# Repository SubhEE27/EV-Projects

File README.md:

# ⚡ Electric Vehicle Projects 🚗

This repository showcases my work in **Electric Vehicle (EV) system design**, focusing on **MATLAB/Simulink simulations**, **custom PCB development**, and a **3D CAD model** of an e-rickshaw. These projects combine theoretical modeling with hands-on engineering to develop subsystems of electric mobility solutions.

---

## 🛠️ Technologies & Tools Used

- **Simulation:** MATLAB/Simulink
- **PCB Design:** Autodesk Eagle, Fusion 360 Electronics
- **3D CAD Modeling:** Autodesk Fusion 360
- **Microcontroller Integration:** Arduino, ESP32

---

## 📁 Repository Structure

/MATLAB_Simulations/
├── BLDC_Motor_Control/
├── Power_Management_System/
└── Regenerative_Braking_Model/

/PCB_Designs/
├── Motor_Controller_PCB/
└── Battery_Management_PCB/

/3D_CAD_Model/
└── E_Rickshaw_Model.f3d

---

## ⚙️ Project Highlights

### 🔷 MATLAB/Simulink Simulations

1. **BLDC Motor Control**
   - Implemented 6-step commutation with inverter, PI control loop, and DC-link filtering
   - Simulated torque and speed control for efficient motor drive

---

### 🟢 PCB Development

1. **Motor Controller PCB**
   - Designed multi-layer PCB with gate drivers, MOSFETs, and microcontroller interface
   - Integrated feedback sensors and protection circuitry
     
---

### 🟠 3D CAD: E-Rickshaw Model

- Created a **full 3D assembly model** of an e-rickshaw using **Fusion 360**
- Includes chassis, battery housing, motor mount, and cabin
- Useful for mechanical layout planning and integration with electronics

---

## 🚀 Getting Started

### Requirements
- MATLAB R2021b or later with Simscape and Simulink
- Autodesk Eagle or Fusion 360 for PCB and CAD files
- LTspice (optional for analog circuit validation)

### How to Use
- Open `.slx` files in MATLAB/Simulink to simulate system behavior
- Open `.brd` or `.f3d` files in Eagle or Fusion 360 for design viewing or editing
- Each folder contains documentation, schematics, and simulation data

---

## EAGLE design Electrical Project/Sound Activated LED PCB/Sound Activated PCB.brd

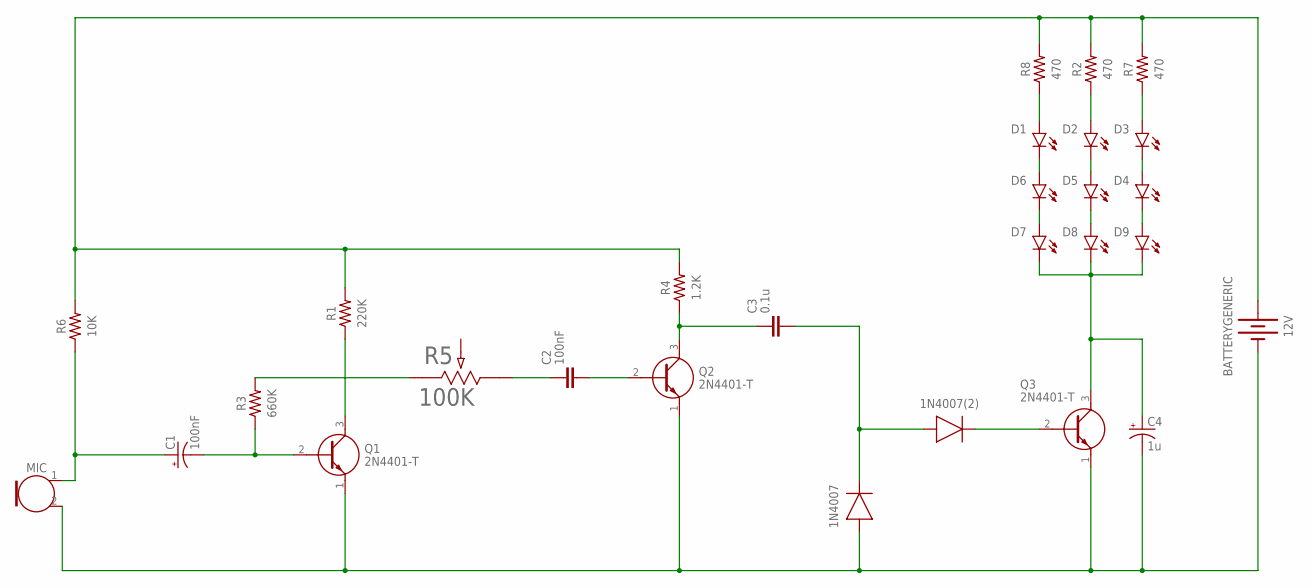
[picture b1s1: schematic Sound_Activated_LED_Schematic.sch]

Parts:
1N4007, 1N4007(2): DIODE_1N4148W-7-F_SOD123G; SOD3715X135
12V: BATTERYGENERIC; BATTERY-GENERIC
C1: 100nF; CAPMP3216X180N
C2: 100nF; CAPC1005X60
C3: 0.1u; CAPC1005X60
C4: 1u; CAPMP3216X180N
D1, D2, D3, D4, D5, D6, D7, D8, D9: CHIP-ROUND-R_0603; LEDC1608X65N_RND-R
MIC: CMA-4544PF-W
Q1, Q2, Q3: 2N4401-T; 2N4401T
R1: 220K; RESC1005X40
R2, R7, R8: 470; RESC1005X40
R3: 660K; RESC1005X40
R4: 1.2K; RESC1005X40
R5: 100K; POT_1623757-2
R6: 10K; RESC1005X40

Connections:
unnamed: C1.1 (+), MIC.1 (OUT), R6.1
unnamed: D1.A, R8.1
unnamed: Q1.3 (C), R1.1
unnamed: 1N4007.2 (A), 12V.-, C4.2 (-), MIC.2 (GND), Q1.1 (E), Q2.1 (E), Q3.1 (E)
unnamed: C1.2 (-), Q1.2 (B), R3.1
unnamed: R3.2, R5.1
unnamed: C2.1, R5.3
unnamed: C2.2, Q2.2 (B)
unnamed: C3.1, Q2.3 (C), R4.1
unnamed: 12V.+, R1.2, R2.2, R4.2, R6.2, R7.2, R8.2
unnamed: D2.A, R2.1
unnamed: D3.A, R7.1
unnamed: D1.C, D6.A
unnamed: D2.C, D5.A
unnamed: D3.C, D4.A
unnamed: D6.C, D7.A
unnamed: D5.C, D8.A
unnamed: D4.C, D9.A
unnamed: C4.1 (+), D7.C, D8.C, D9.C, Q3.3 (C)
unnamed: 1N4007.1 (C), 1N4007(2).2 (A), C3.2
unnamed: 1N4007(2).1 (C), Q3.2 (B)

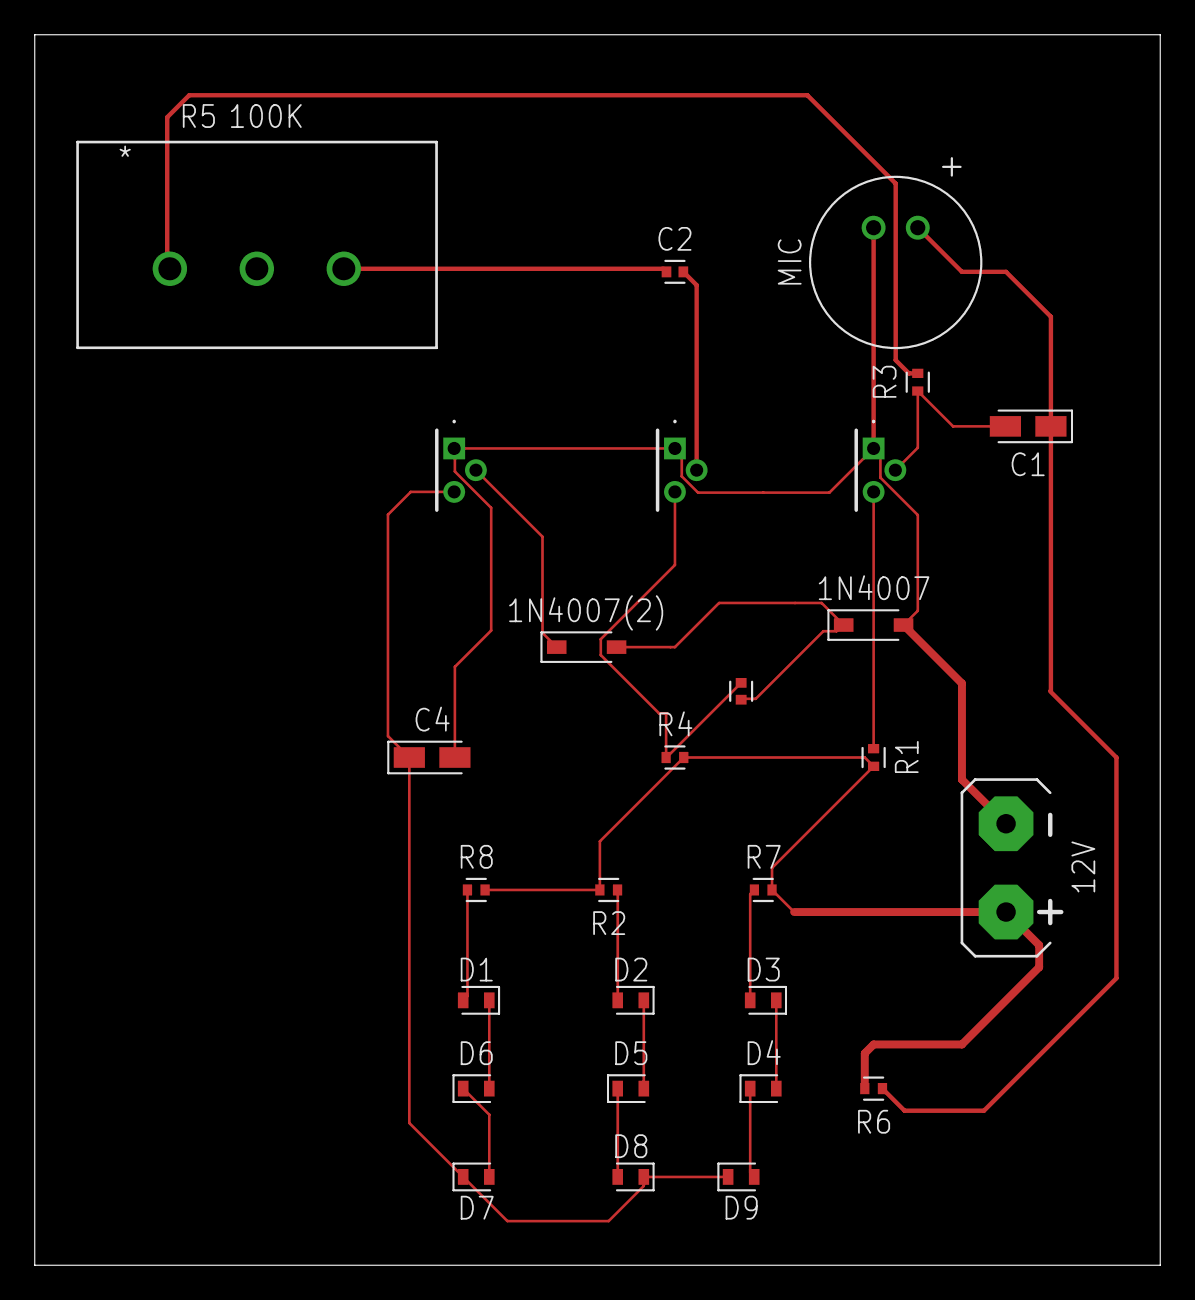
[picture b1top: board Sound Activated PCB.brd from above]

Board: 2 copper layers, 64.8 x 70.8 mm, 28 parts (0 on the bottom side), 21 nets.

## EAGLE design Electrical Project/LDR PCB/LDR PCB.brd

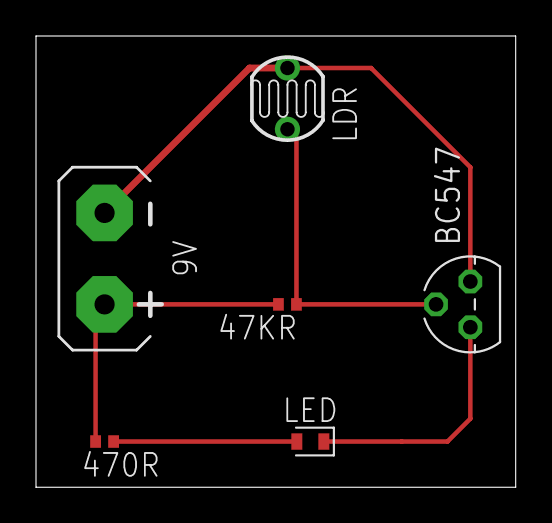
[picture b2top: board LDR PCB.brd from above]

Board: 2 copper layers, 26.6 x 25.1 mm, 6 parts (0 on the bottom side), 5 nets.

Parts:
9V: BATTERY-9VGENERIC; BATTERY-GENERIC
47KR: 47K; R0402
470R: 470; R0402
BC547: BC547; TO92
LDR: PHOTOCELL_GL5528; GL5528
LED: CHIP-ROUND-R_0603; LEDC1608X65N_RND-R

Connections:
unnamed: 9V.-, BC547.1, LDR.2
unnamed: 47KR.1, BC547.2, LDR.1
unnamed: BC547.3, LED.C
unnamed: 470R.1, LED.A
unnamed: 9V.+, 47KR.2, 470R.2

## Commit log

2025-07-17 README.md
2025-07-17 gfb.txt
2025-07-17 gvg.txt
2025-07-17 gfg.txt
2025-07-17 fg.txt
2025-07-17 hgh.txt

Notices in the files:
parts and their libraries:
COPYRIGHT: Copyright (C) 2016 Accelerated Designs. All rights reserved
